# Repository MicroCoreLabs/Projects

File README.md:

# Ted Fried's MicroCore Labs Projects

My blog which has some details on these projects: www.MicroCoreLabs.Wordpress.com

My YouTube Channel with some videos of the stuff in action: www.youtube.com/channel/UC9B3TaEUon-araO2j7tp9jg/videos

Boards:

    MCL6809     -  Motorola 6809E emulator which runs on a Teensy 4.1 and can be used as a drop-in replacment 
    MCLZ8       -  Zilog Z80 emulator which runs on a Teensy 4.1 and can be used as a drop-in replacment 
    MCL86+      -  Intel 8088 emulator which runs on a Teensy 4.1 and can be used as a drop-in replacment 
    MCL86jr     -  IBMPCjr Accelerator which boosts performance to IBM PC/AT speed
    MCL65+      -  MOS 6502 emulator which runs on a Teensy 4.1 and can be used as a 6502 drop-in replacment
    MCL64       -  MOS 6510 emulator which runs on a Teensy 4.1 and can be used as a drop-in replacment in the Commodore 64
    MCL68+      -  Motorola 68000 emulator which runs on a Teensy 4.1 and can be used as a drop-in replacment 
    MCLV20_Max  -  NEC V20 drop-in replacment CPU which uses the MCL86+ board
	MCL8080+    -  Intel 8080 emulator which runs on an ATTiny85 and has a SPI interface as the local bus

Emulated Processors:

    MCL68  - Motorola 68000 Emulator written in C
    RISCV  - Simple and compact RISC-V RS32I implementation written in C
    MCL65  - MOS 6502 written in C

Microsequencer-based processors: 

    MCL65 - MOS 6502 
    MCL51 - Intel 8051
    MCL86 - Intel 8086/8088
    
Other processors:

    MCLR5 - Quad-Issue Superscalar RISCV
    Lockstep Quad Modular Redundant System 
    
Misc:

    Wheelwriter  - FPGA based Printer Option for the IBM Wheelwriter 5
    Wheelwriter2 - Arduino Leonardo based Printer Option for the IBM Wheelwriter 5
    Brother Typewriter - Arduino Leonardo converts Serial RX to a Brother Word Processor
    EPROM Emulator - Small PCB which uses Teensy 4.0 to emulate up a 64KB 27C512 EPROM
    MCL64_Tester - Extensive, menu-based, tests for the Commodore 64 motherboard
    MCLZ8 TRS-80 Emulator - Emulates a TRS-80 Model 1 inside of a Teensy microcontroller board
    MCL_TRS_NABU - Emulates a TRS-80 Model 1 using the MCLZ8 which runs inside of a NABU Personal Computer
    Turbo NABU - Uses the MCLZ8 to run simple C code on the Teensy to control the motherboard resources of the NABU Computer
    MDA Video - Project which uses an Arty Z7-20 SOC FPGA board to diaplay BMP images to an MDA display
    IBMPC_68000 - Uses the MCL86+ board to emulate a Motorola 68000 which runs inside of an IBM PC as-if they selected this processor in 1981
    MCL65_Apple1 - Converts an Apple II into an Appke 1 by emulating the BIOS PROMs, system memory, and performing some I/O conversion
	XTMax - 8-bit ISA card containing a Teensy 4.1 which can emulate RAM, ROM, and peripherals
        
For questions email me at www.MicroCoreLabs.com

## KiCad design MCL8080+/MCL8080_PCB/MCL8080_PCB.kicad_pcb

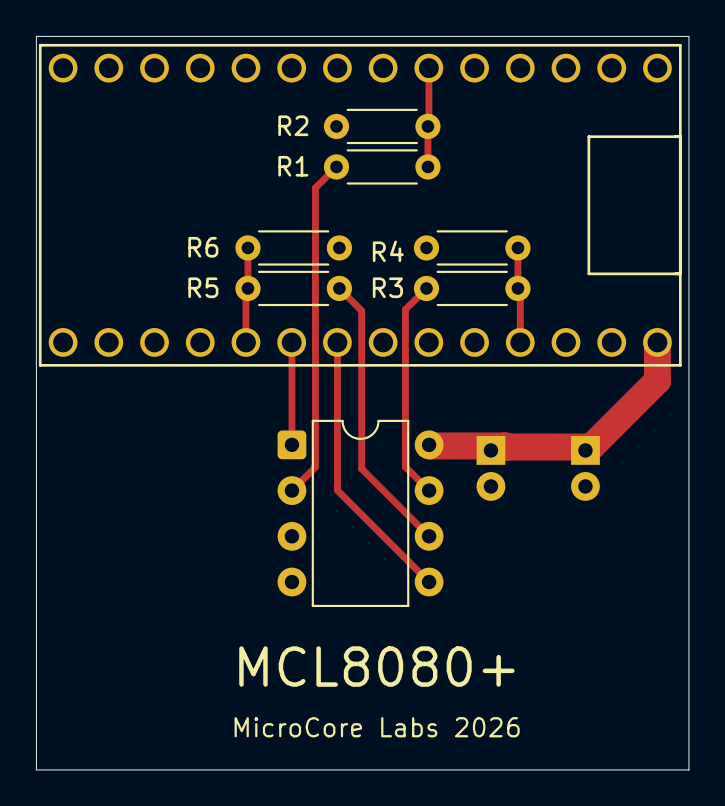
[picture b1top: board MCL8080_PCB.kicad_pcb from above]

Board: 2 copper layers, 36.2 x 40.8 mm, 10 parts (0 on the bottom side), 10 nets.

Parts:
C1: 0.1uF; CP_Radial_D5.0mm_P2.00mm
C2: 10 uF; CP_Radial_D5.0mm_P2.00mm
R1, R3, R5: 680; R_Axial_DIN0204_L3.6mm_D1.6mm_P5.08mm_Horizontal
R2, R4, R6: 1.2K; R_Axial_DIN0204_L3.6mm_D1.6mm_P5.08mm_Horizontal
U1: ATtiny85V-10P; DIP-8_W7.62mm
U2: Teensy4.0; Teensy40

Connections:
+5V: C1.1, C2.1, U1.8 (VCC), U2.33 (VIN)
GND: C1.2, C2.2, R2.1, R4.1, R6.1, U1.4 (GND), U2.1 (GND), U2.32 (GND)
RESET_n_3V: U1.1 (~RESET/PB5), U2.25 (18_A4_SDA0)
SPI_CLK_3V: R3.1, R4.2, U2.30 (23_A9_CRX1_MCLK1)
SPI_CLK_5V: R3.2, U1.7 (PB2)
SPI_CS_n_3V: R1.1, R2.2, U2.6 (4_BCLK2)
SPI_CS_n_5V: R1.2, U1.2 (XTAL1/PB3)
SPI_MISO_3V: U1.5 (AREF/PB0), U2.26 (19_A5_SCL0)
SPI_MOSI_3V: R5.1, R6.2, U2.24 (17_A3_TX4_SDA1)
SPI_MOSI_5V: R5.2, U1.6 (PB1)

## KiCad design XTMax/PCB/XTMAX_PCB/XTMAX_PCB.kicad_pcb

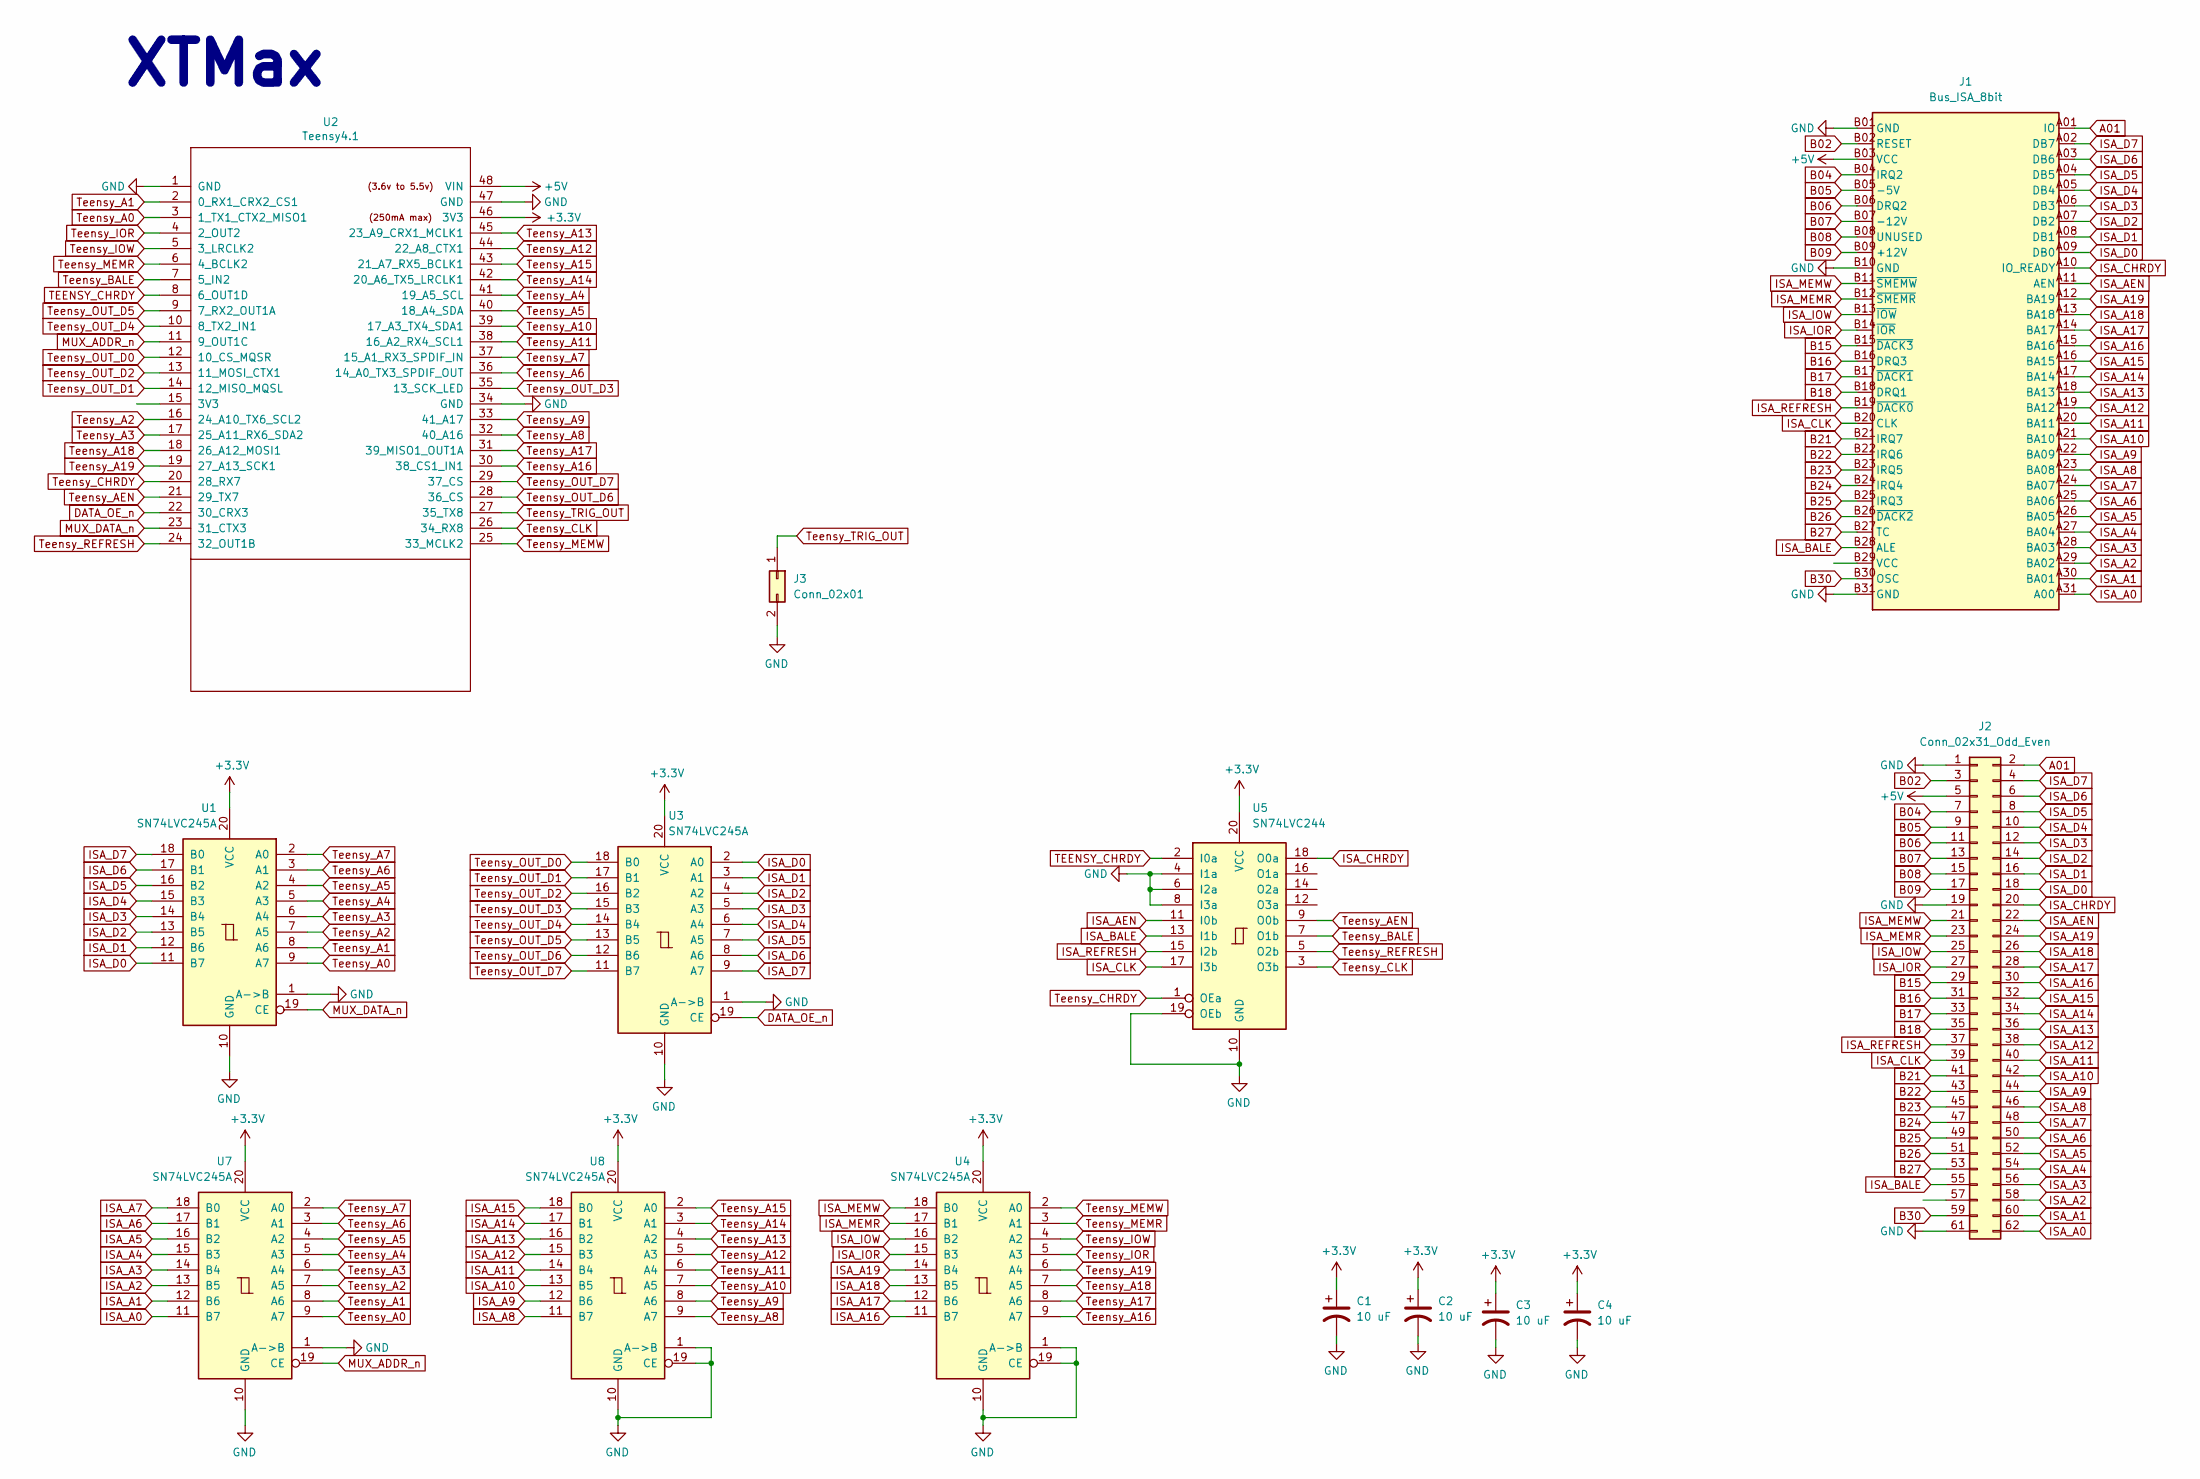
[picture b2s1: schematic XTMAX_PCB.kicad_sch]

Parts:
C1, C2, C3, C4: 10 uF; C_0402_1005Metric
J1: Bus_ISA_8bit; isa
J2: Conn_02x31_Odd_Even; PinHeader_2x31_P2.54mm_Vertical
J3: Conn_02x01; PinHeader_2x01_P2.54mm_Vertical
U1, U3, U4, U7, U8: SN74LVC245A; TSSOP-20_4.4x6.5mm_P0.65mm
U2: Teensy4.1; Teensy41_Ted_Modified
U5: SN74LVC244; TSSOP-20_4.4x6.5mm_P0.65mm

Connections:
+3V3: C1.1, C2.1, C3.1, C4.1, U1.20 (VCC), U2.46 (3V3), U3.20 (VCC), U4.20 (VCC), U5.20 (VCC), U7.20 (VCC), U8.20 (VCC)
+5V: J1.B03 (VCC), J2.5, U2.48 (VIN)
A01: J1.A01 (IO), J2.2
B02: J1.B02 (RESET), J2.3
B04: J1.B04 (IRQ2), J2.7
B05: J1.B05 (-5V), J2.9
B06: J1.B06 (DRQ2), J2.11
B07: J1.B07 (-12V), J2.13
B08: J1.B08 (UNUSED), J2.15
B09: J1.B09 (+12V), J2.17
B15: J1.B15 (~DACK3), J2.29
B16: J1.B16 (DRQ3), J2.31
B17: J1.B17 (~DACK1), J2.33
B18: J1.B18 (DRQ1), J2.35
B21: J1.B21 (IRQ7), J2.41
B22: J1.B22 (IRQ6), J2.43
B23: J1.B23 (IRQ5), J2.45
B24: J1.B24 (IRQ4), J2.47
B25: J1.B25 (IRQ3), J2.49
B26: J1.B26 (~DACK2), J2.51
B27: J1.B27 (TC), J2.53
B30: J1.B30 (OSC), J2.59
DATA_OE_n: U2.22 (30_CRX3), U3.19 (CE)
GND: C1.2, C2.2, C3.2, C4.2, J1.B01 (GND), J1.B10 (GND), J1.B31 (GND), J2.1, J2.19, J2.61, J3.2, U1.1 (A->B), U1.10 (GND), U2.1 (GND), U2.34 (GND), U2.47 (GND), U3.1 (A->B), U3.10 (GND), U4.1 (A->B), U4.10 (GND), U4.19 (CE), U5.4 (I1a), U5.6 (I2a), U5.8 (I3a), U5.10 (GND), U5.19 (OEb), U7.1 (A->B), U7.10 (GND), U8.1 (A->B), U8.10 (GND), U8.19 (CE)
ISA_A0: J1.A31 (A00), J2.62, U7.11 (B7)
ISA_A1: J1.A30 (BA01), J2.60, U7.12 (B6)
ISA_A2: J1.A29 (BA02), J2.58, U7.13 (B5)
ISA_A3: J1.A28 (BA03), J2.56, U7.14 (B4)
ISA_A4: J1.A27 (BA04), J2.54, U7.15 (B3)
ISA_A5: J1.A26 (BA05), J2.52, U7.16 (B2)
ISA_A6: J1.A25 (BA06), J2.50, U7.17 (B1)
ISA_A7: J1.A24 (BA07), J2.48, U7.18 (B0)
ISA_A8: J1.A23 (BA08), J2.46, U8.11 (B7)
ISA_A9: J1.A22 (BA09), J2.44, U8.12 (B6)
ISA_A10: J1.A21 (BA10), J2.42, U8.13 (B5)
ISA_A11: J1.A20 (BA11), J2.40, U8.14 (B4)
ISA_A12: J1.A19 (BA12), J2.38, U8.15 (B3)
ISA_A13: J1.A18 (BA13), J2.36, U8.16 (B2)
ISA_A14: J1.A17 (BA14), J2.34, U8.17 (B1)
ISA_A15: J1.A16 (BA15), J2.32, U8.18 (B0)
ISA_A16: J1.A15 (BA16), J2.30, U4.11 (B7)
ISA_A17: J1.A14 (BA17), J2.28, U4.12 (B6)
ISA_A18: J1.A13 (BA18), J2.26, U4.13 (B5)
ISA_A19: J1.A12 (BA19), J2.24, U4.14 (B4)
ISA_AEN: J1.A11 (AEN), J2.22, U5.11 (I0b)
ISA_BALE: J1.B28 (ALE), J2.55, U5.13 (I1b)
ISA_CHRDY: J1.A10 (IO_READY), J2.20, U5.18 (O0a)
ISA_CLK: J1.B20 (CLK), J2.39, U5.17 (I3b)
ISA_D0: J1.A09 (DB0), J2.18, U1.11 (B7), U3.2 (A0)
ISA_D1: J1.A08 (DB1), J2.16, U1.12 (B6), U3.3 (A1)
ISA_D2: J1.A07 (DB2), J2.14, U1.13 (B5), U3.4 (A2)
ISA_D3: J1.A06 (DB3), J2.12, U1.14 (B4), U3.5 (A3)
ISA_D4: J1.A05 (DB4), J2.10, U1.15 (B3), U3.6 (A4)
ISA_D5: J1.A04 (DB5), J2.8, U1.16 (B2), U3.7 (A5)
ISA_D6: J1.A03 (DB6), J2.6, U1.17 (B1), U3.8 (A6)
ISA_D7: J1.A02 (DB7), J2.4, U1.18 (B0), U3.9 (A7)
ISA_IOR: J1.B14 (~IOR), J2.27, U4.15 (B3)
ISA_IOW: J1.B13 (~IOW), J2.25, U4.16 (B2)
ISA_MEMR: J1.B12 (~SMEMR), J2.23, U4.17 (B1)
ISA_MEMW: J1.B11 (~SMEMW), J2.21, U4.18 (B0)
ISA_REFRESH: J1.B19 (~DACK0), J2.37, U5.15 (I2b)
MUX_ADDR_n: U2.11 (9_OUT1C), U7.19 (CE)
MUX_DATA_n: U1.19 (CE), U2.23 (31_CTX3)
TEENSY_CHRDY: U2.8 (6_OUT1D), U5.2 (I0a)
Teensy_A0: U1.9 (A7), U2.3 (1_TX1_CTX2_MISO1), U7.9 (A7)
Teensy_A1: U1.8 (A6), U2.2 (0_RX1_CRX2_CS1), U7.8 (A6)
Teensy_A2: U1.7 (A5), U2.16 (24_A10_TX6_SCL2), U7.7 (A5)
Teensy_A3: U1.6 (A4), U2.17 (25_A11_RX6_SDA2), U7.6 (A4)
Teensy_A4: U1.5 (A3), U2.41 (19_A5_SCL), U7.5 (A3)
Teensy_A5: U1.4 (A2), U2.40 (18_A4_SDA), U7.4 (A2)
Teensy_A6: U1.3 (A1), U2.36 (14_A0_TX3_SPDIF_OUT), U7.3 (A1)
Teensy_A7: U1.2 (A0), U2.37 (15_A1_RX3_SPDIF_IN), U7.2 (A0)
Teensy_A8: U2.32 (40_A16), U8.9 (A7)
Teensy_A9: U2.33 (41_A17), U8.8 (A6)
Teensy_A10: U2.39 (17_A3_TX4_SDA1), U8.7 (A5)
Teensy_A11: U2.38 (16_A2_RX4_SCL1), U8.6 (A4)
Teensy_A12: U2.44 (22_A8_CTX1), U8.5 (A3)
Teensy_A13: U2.45 (23_A9_CRX1_MCLK1), U8.4 (A2)
Teensy_A14: U2.42 (20_A6_TX5_LRCLK1), U8.3 (A1)
Teensy_A15: U2.43 (21_A7_RX5_BCLK1), U8.2 (A0)
Teensy_A16: U2.30 (38_CS1_IN1), U4.9 (A7)
Teensy_A17: U2.31 (39_MISO1_OUT1A), U4.8 (A6)
Teensy_A18: U2.18 (26_A12_MOSI1), U4.7 (A5)
Teensy_A19: U2.19 (27_A13_SCK1), U4.6 (A4)
Teensy_AEN: U2.21 (29_TX7), U5.9 (O0b)
Teensy_BALE: U2.7 (5_IN2), U5.7 (O1b)
Teensy_CHRDY: U2.20 (28_RX7), U5.1 (OEa)
Teensy_CLK: U2.26 (34_RX8), U5.3 (O3b)
Teensy_IOR: U2.4 (2_OUT2), U4.5 (A3)
Teensy_IOW: U2.5 (3_LRCLK2), U4.4 (A2)
Teensy_MEMR: U2.6 (4_BCLK2), U4.3 (A1)
Teensy_MEMW: U2.25 (33_MCLK2), U4.2 (A0)
Teensy_OUT_D0: U2.12 (10_CS_MQSR), U3.18 (B0)
Teensy_OUT_D1: U2.14 (12_MISO_MQSL), U3.17 (B1)
Teensy_OUT_D2: U2.13 (11_MOSI_CTX1), U3.16 (B2)
Teensy_OUT_D3: U2.35 (13_SCK_LED), U3.15 (B3)
Teensy_OUT_D4: U2.10 (8_TX2_IN1), U3.14 (B4)
Teensy_OUT_D5: U2.9 (7_RX2_OUT1A), U3.13 (B5)
Teensy_OUT_D6: U2.28 (36_CS), U3.12 (B6)
Teensy_OUT_D7: U2.29 (37_CS), U3.11 (B7)
Teensy_REFRESH: U2.24 (32_OUT1B), U5.5 (O2b)
Teensy_TRIG_OUT: J3.1, U2.27 (35_TX8)

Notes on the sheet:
XTMax

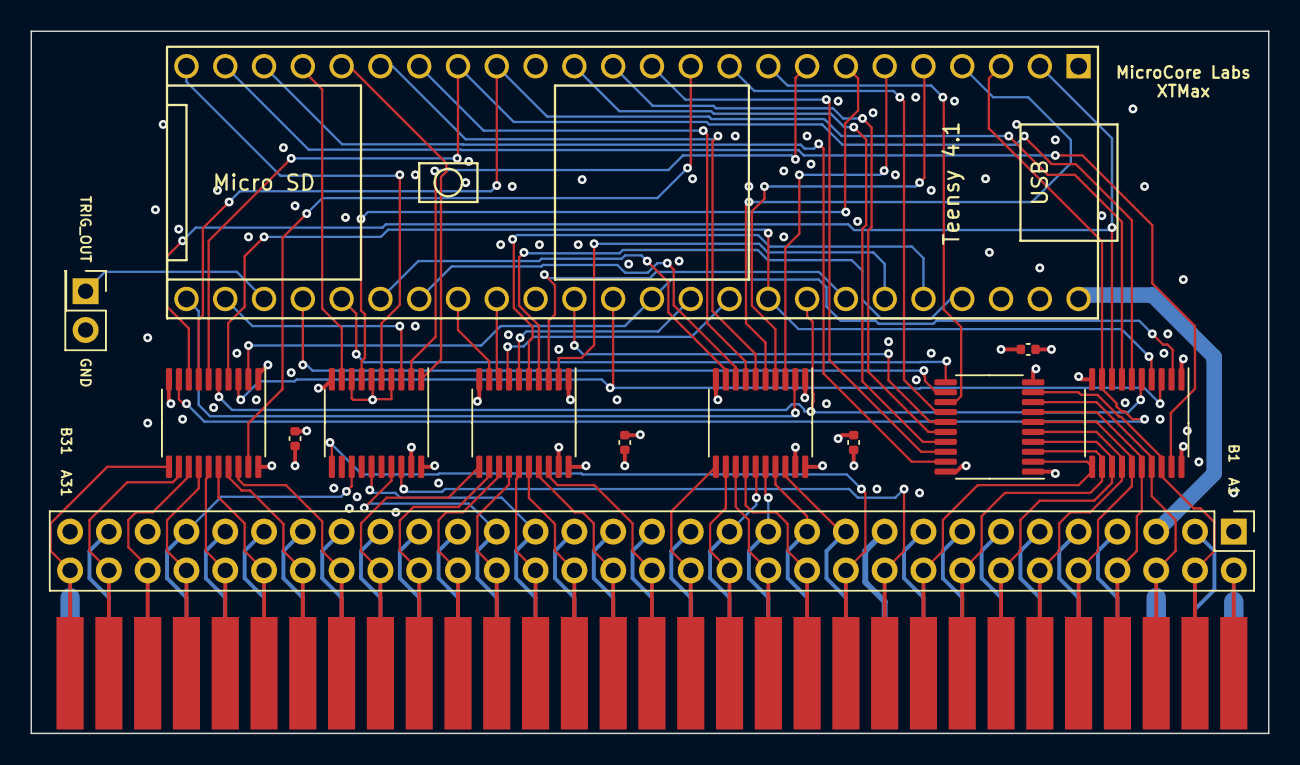
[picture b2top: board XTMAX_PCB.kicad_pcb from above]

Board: 4 copper layers, 81.0 x 46.0 mm, 14 parts (0 on the bottom side), 102 nets.

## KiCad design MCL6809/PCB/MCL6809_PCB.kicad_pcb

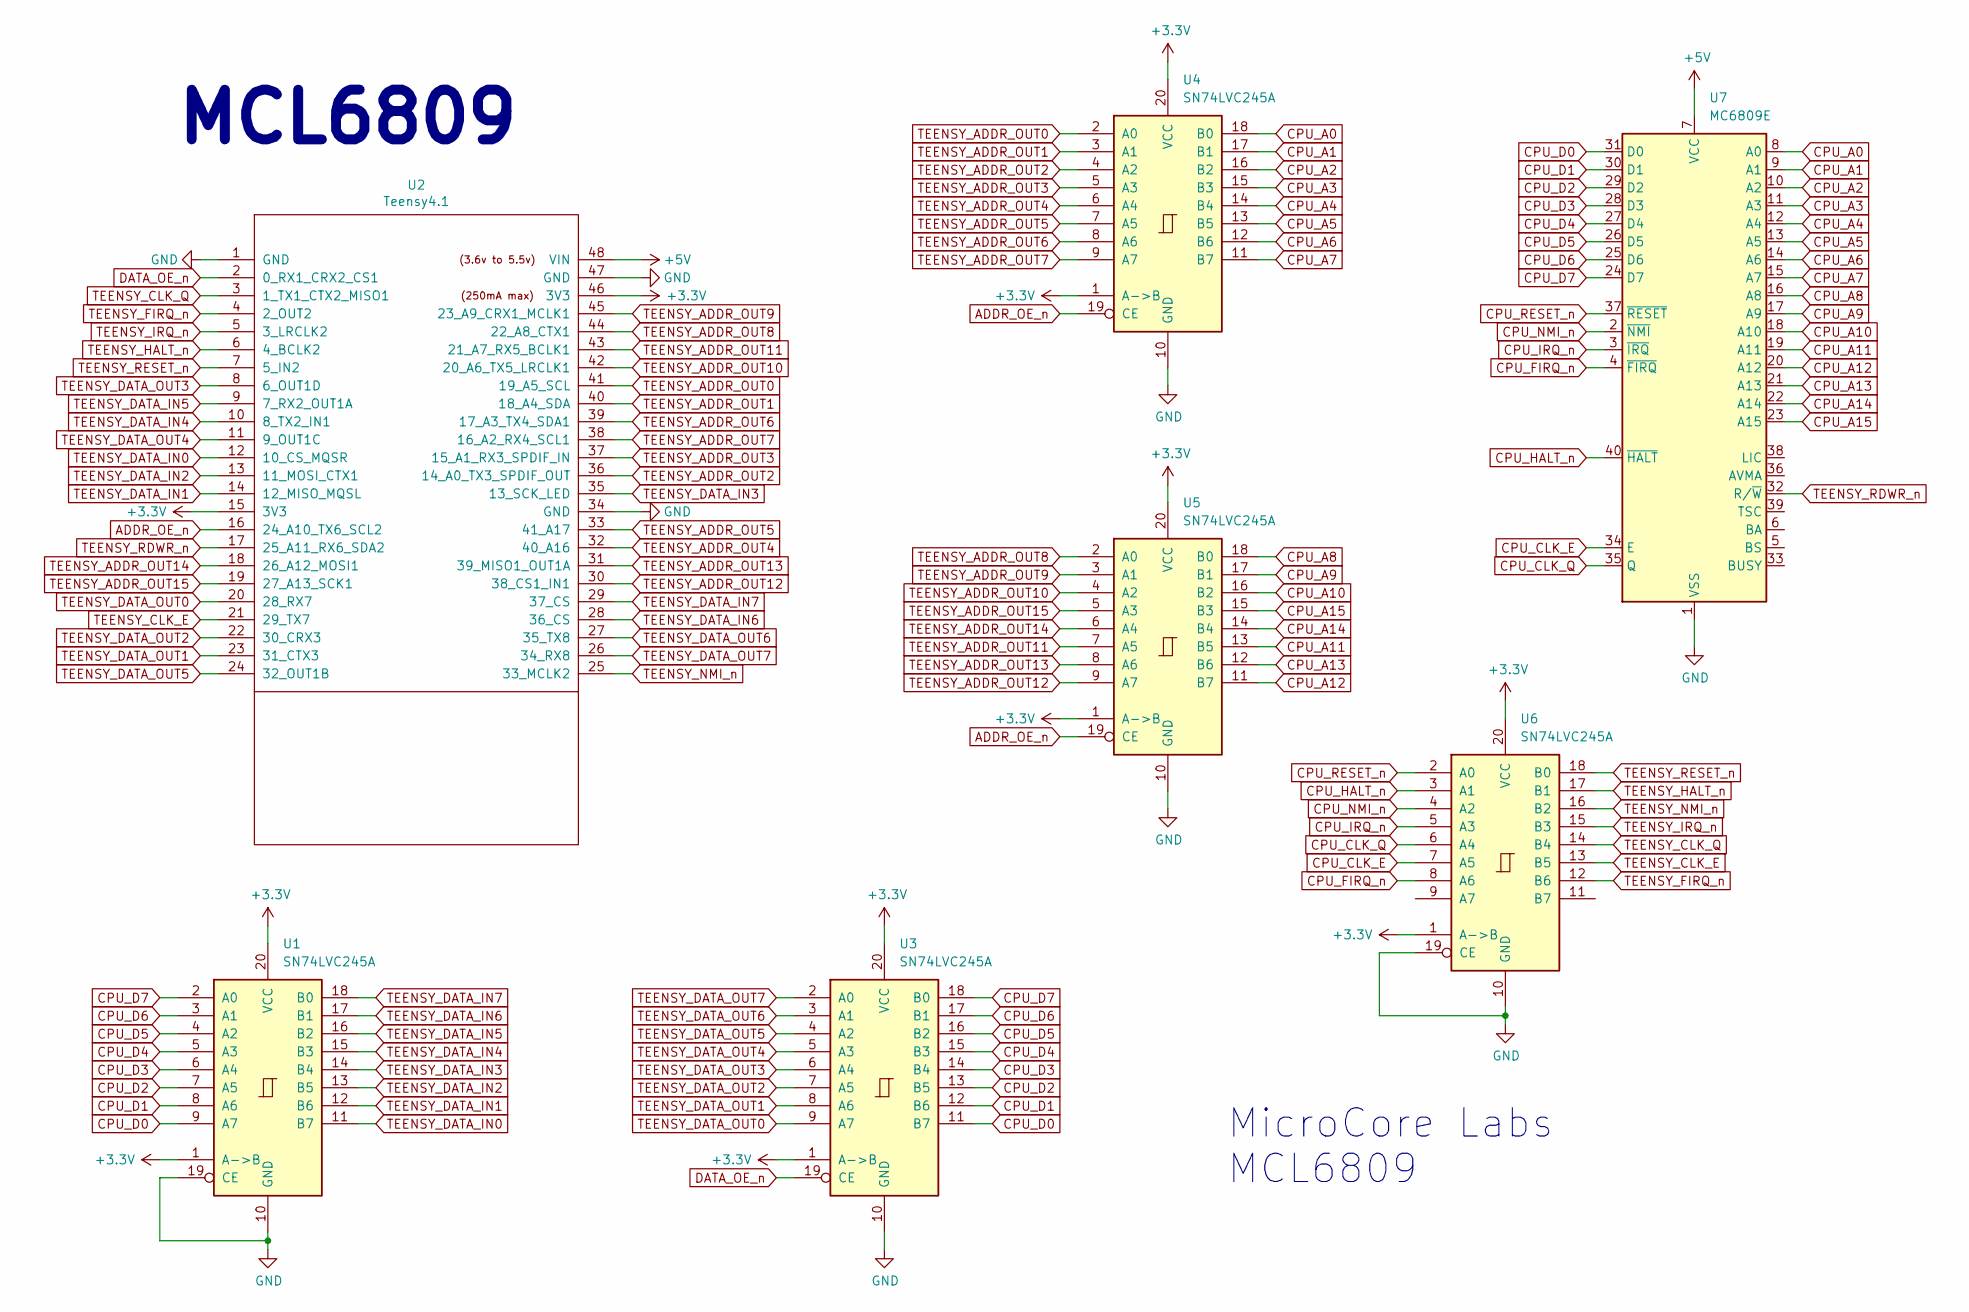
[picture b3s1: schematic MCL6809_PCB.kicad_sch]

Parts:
U1, U3, U4, U5, U6: SN74LVC245A; TSSOP-20_4.4x6.5mm_P0.65mm
U2: Teensy4.1; Teensy41_Ted_Modified
U7: MC6809E; DIP-40_W15.24mm

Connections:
+3V3: U1.1 (A->B), U1.20 (VCC), U2.15 (3V3), U2.46 (3V3), U3.1 (A->B), U3.20 (VCC), U4.1 (A->B), U4.20 (VCC), U5.1 (A->B), U5.20 (VCC), U6.1 (A->B), U6.20 (VCC)
+5V: U2.48 (VIN), U7.7 (VCC)
ADDR_OE_n: U2.16 (24_A10_TX6_SCL2), U4.19 (CE), U5.19 (CE)
CPU_A0: U4.18 (B0), U7.8 (A0)
CPU_A1: U4.17 (B1), U7.9 (A1)
CPU_A2: U4.16 (B2), U7.10 (A2)
CPU_A3: U4.15 (B3), U7.11 (A3)
CPU_A4: U4.14 (B4), U7.12 (A4)
CPU_A5: U4.13 (B5), U7.13 (A5)
CPU_A6: U4.12 (B6), U7.14 (A6)
CPU_A7: U4.11 (B7), U7.15 (A7)
CPU_A8: U5.18 (B0), U7.16 (A8)
CPU_A9: U5.17 (B1), U7.17 (A9)
CPU_A10: U5.16 (B2), U7.18 (A10)
CPU_A11: U5.13 (B5), U7.19 (A11)
CPU_A12: U5.11 (B7), U7.20 (A12)
CPU_A13: U5.12 (B6), U7.21 (A13)
CPU_A14: U5.14 (B4), U7.22 (A14)
CPU_A15: U5.15 (B3), U7.23 (A15)
CPU_CLK_E: U6.7 (A5), U7.34 (E)
CPU_CLK_Q: U6.6 (A4), U7.35 (Q)
CPU_D0: U1.9 (A7), U3.11 (B7), U7.31 (D0)
CPU_D1: U1.8 (A6), U3.12 (B6), U7.30 (D1)
CPU_D2: U1.7 (A5), U3.13 (B5), U7.29 (D2)
CPU_D3: U1.6 (A4), U3.14 (B4), U7.28 (D3)
CPU_D4: U1.5 (A3), U3.15 (B3), U7.27 (D4)
CPU_D5: U1.4 (A2), U3.16 (B2), U7.26 (D5)
CPU_D6: U1.3 (A1), U3.17 (B1), U7.25 (D6)
CPU_D7: U1.2 (A0), U3.18 (B0), U7.24 (D7)
CPU_FIRQ_n: U6.8 (A6), U7.4 (~FIRQ)
CPU_HALT_n: U6.3 (A1), U7.40 (~HALT)
CPU_IRQ_n: U6.5 (A3), U7.3 (~IRQ)
CPU_NMI_n: U6.4 (A2), U7.2 (~NMI)
CPU_RESET_n: U6.2 (A0), U7.37 (~RESET)
DATA_OE_n: U2.2 (0_RX1_CRX2_CS1), U3.19 (CE)
GND: U1.10 (GND), U1.19 (CE), U2.1 (GND), U2.34 (GND), U2.47 (GND), U3.10 (GND), U4.10 (GND), U5.10 (GND), U6.10 (GND), U6.19 (CE), U7.1 (VSS)
TEENSY_ADDR_OUT0: U2.41 (19_A5_SCL), U4.2 (A0)
TEENSY_ADDR_OUT1: U2.40 (18_A4_SDA), U4.3 (A1)
TEENSY_ADDR_OUT2: U2.36 (14_A0_TX3_SPDIF_OUT), U4.4 (A2)
TEENSY_ADDR_OUT3: U2.37 (15_A1_RX3_SPDIF_IN), U4.5 (A3)
TEENSY_ADDR_OUT4: U2.32 (40_A16), U4.6 (A4)
TEENSY_ADDR_OUT5: U2.33 (41_A17), U4.7 (A5)
TEENSY_ADDR_OUT6: U2.39 (17_A3_TX4_SDA1), U4.8 (A6)
TEENSY_ADDR_OUT7: U2.38 (16_A2_RX4_SCL1), U4.9 (A7)
TEENSY_ADDR_OUT8: U2.44 (22_A8_CTX1), U5.2 (A0)
TEENSY_ADDR_OUT9: U2.45 (23_A9_CRX1_MCLK1), U5.3 (A1)
TEENSY_ADDR_OUT10: U2.42 (20_A6_TX5_LRCLK1), U5.4 (A2)
TEENSY_ADDR_OUT11: U2.43 (21_A7_RX5_BCLK1), U5.7 (A5)
TEENSY_ADDR_OUT12: U2.30 (38_CS1_IN1), U5.9 (A7)
TEENSY_ADDR_OUT13: U2.31 (39_MISO1_OUT1A), U5.8 (A6)
TEENSY_ADDR_OUT14: U2.18 (26_A12_MOSI1), U5.6 (A4)
TEENSY_ADDR_OUT15: U2.19 (27_A13_SCK1), U5.5 (A3)
TEENSY_CLK_E: U2.21 (29_TX7), U6.13 (B5)
TEENSY_CLK_Q: U2.3 (1_TX1_CTX2_MISO1), U6.14 (B4)
TEENSY_DATA_IN0: U1.11 (B7), U2.12 (10_CS_MQSR)
TEENSY_DATA_IN1: U1.12 (B6), U2.14 (12_MISO_MQSL)
TEENSY_DATA_IN2: U1.13 (B5), U2.13 (11_MOSI_CTX1)
TEENSY_DATA_IN3: U1.14 (B4), U2.35 (13_SCK_LED)
TEENSY_DATA_IN4: U1.15 (B3), U2.10 (8_TX2_IN1)
TEENSY_DATA_IN5: U1.16 (B2), U2.9 (7_RX2_OUT1A)
TEENSY_DATA_IN6: U1.17 (B1), U2.28 (36_CS)
TEENSY_DATA_IN7: U1.18 (B0), U2.29 (37_CS)
TEENSY_DATA_OUT0: U2.20 (28_RX7), U3.9 (A7)
TEENSY_DATA_OUT1: U2.23 (31_CTX3), U3.8 (A6)
TEENSY_DATA_OUT2: U2.22 (30_CRX3), U3.7 (A5)
TEENSY_DATA_OUT3: U2.8 (6_OUT1D), U3.6 (A4)
TEENSY_DATA_OUT4: U2.11 (9_OUT1C), U3.5 (A3)
TEENSY_DATA_OUT5: U2.24 (32_OUT1B), U3.4 (A2)
TEENSY_DATA_OUT6: U2.27 (35_TX8), U3.3 (A1)
TEENSY_DATA_OUT7: U2.26 (34_RX8), U3.2 (A0)
TEENSY_FIRQ_n: U2.4 (2_OUT2), U6.12 (B6)
TEENSY_HALT_n: U2.6 (4_BCLK2), U6.17 (B1)
TEENSY_IRQ_n: U2.5 (3_LRCLK2), U6.15 (B3)
TEENSY_NMI_n: U2.25 (33_MCLK2), U6.16 (B2)
TEENSY_RDWR_n: U2.17 (25_A11_RX6_SDA2), U7.32 (R/~W)
TEENSY_RESET_n: U2.7 (5_IN2), U6.18 (B0)

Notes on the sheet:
MicroCore Labs MCL6809
MCL6809

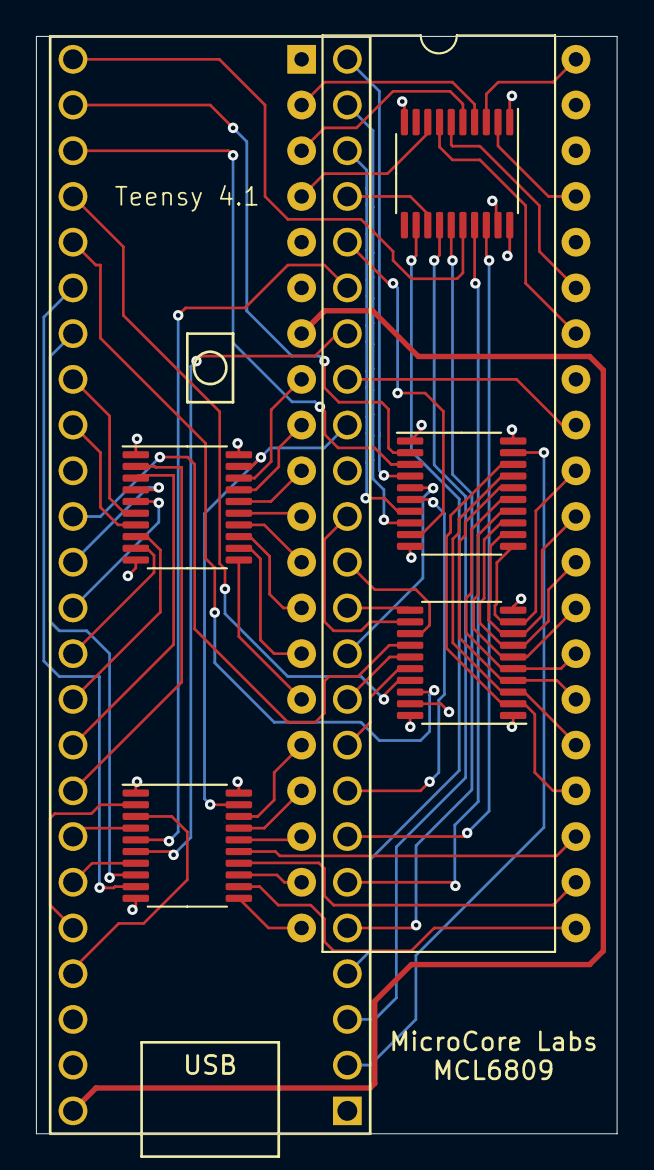
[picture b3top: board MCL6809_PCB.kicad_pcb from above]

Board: 4 copper layers, 32.3 x 61.0 mm, 7 parts (0 on the bottom side), 76 nets.

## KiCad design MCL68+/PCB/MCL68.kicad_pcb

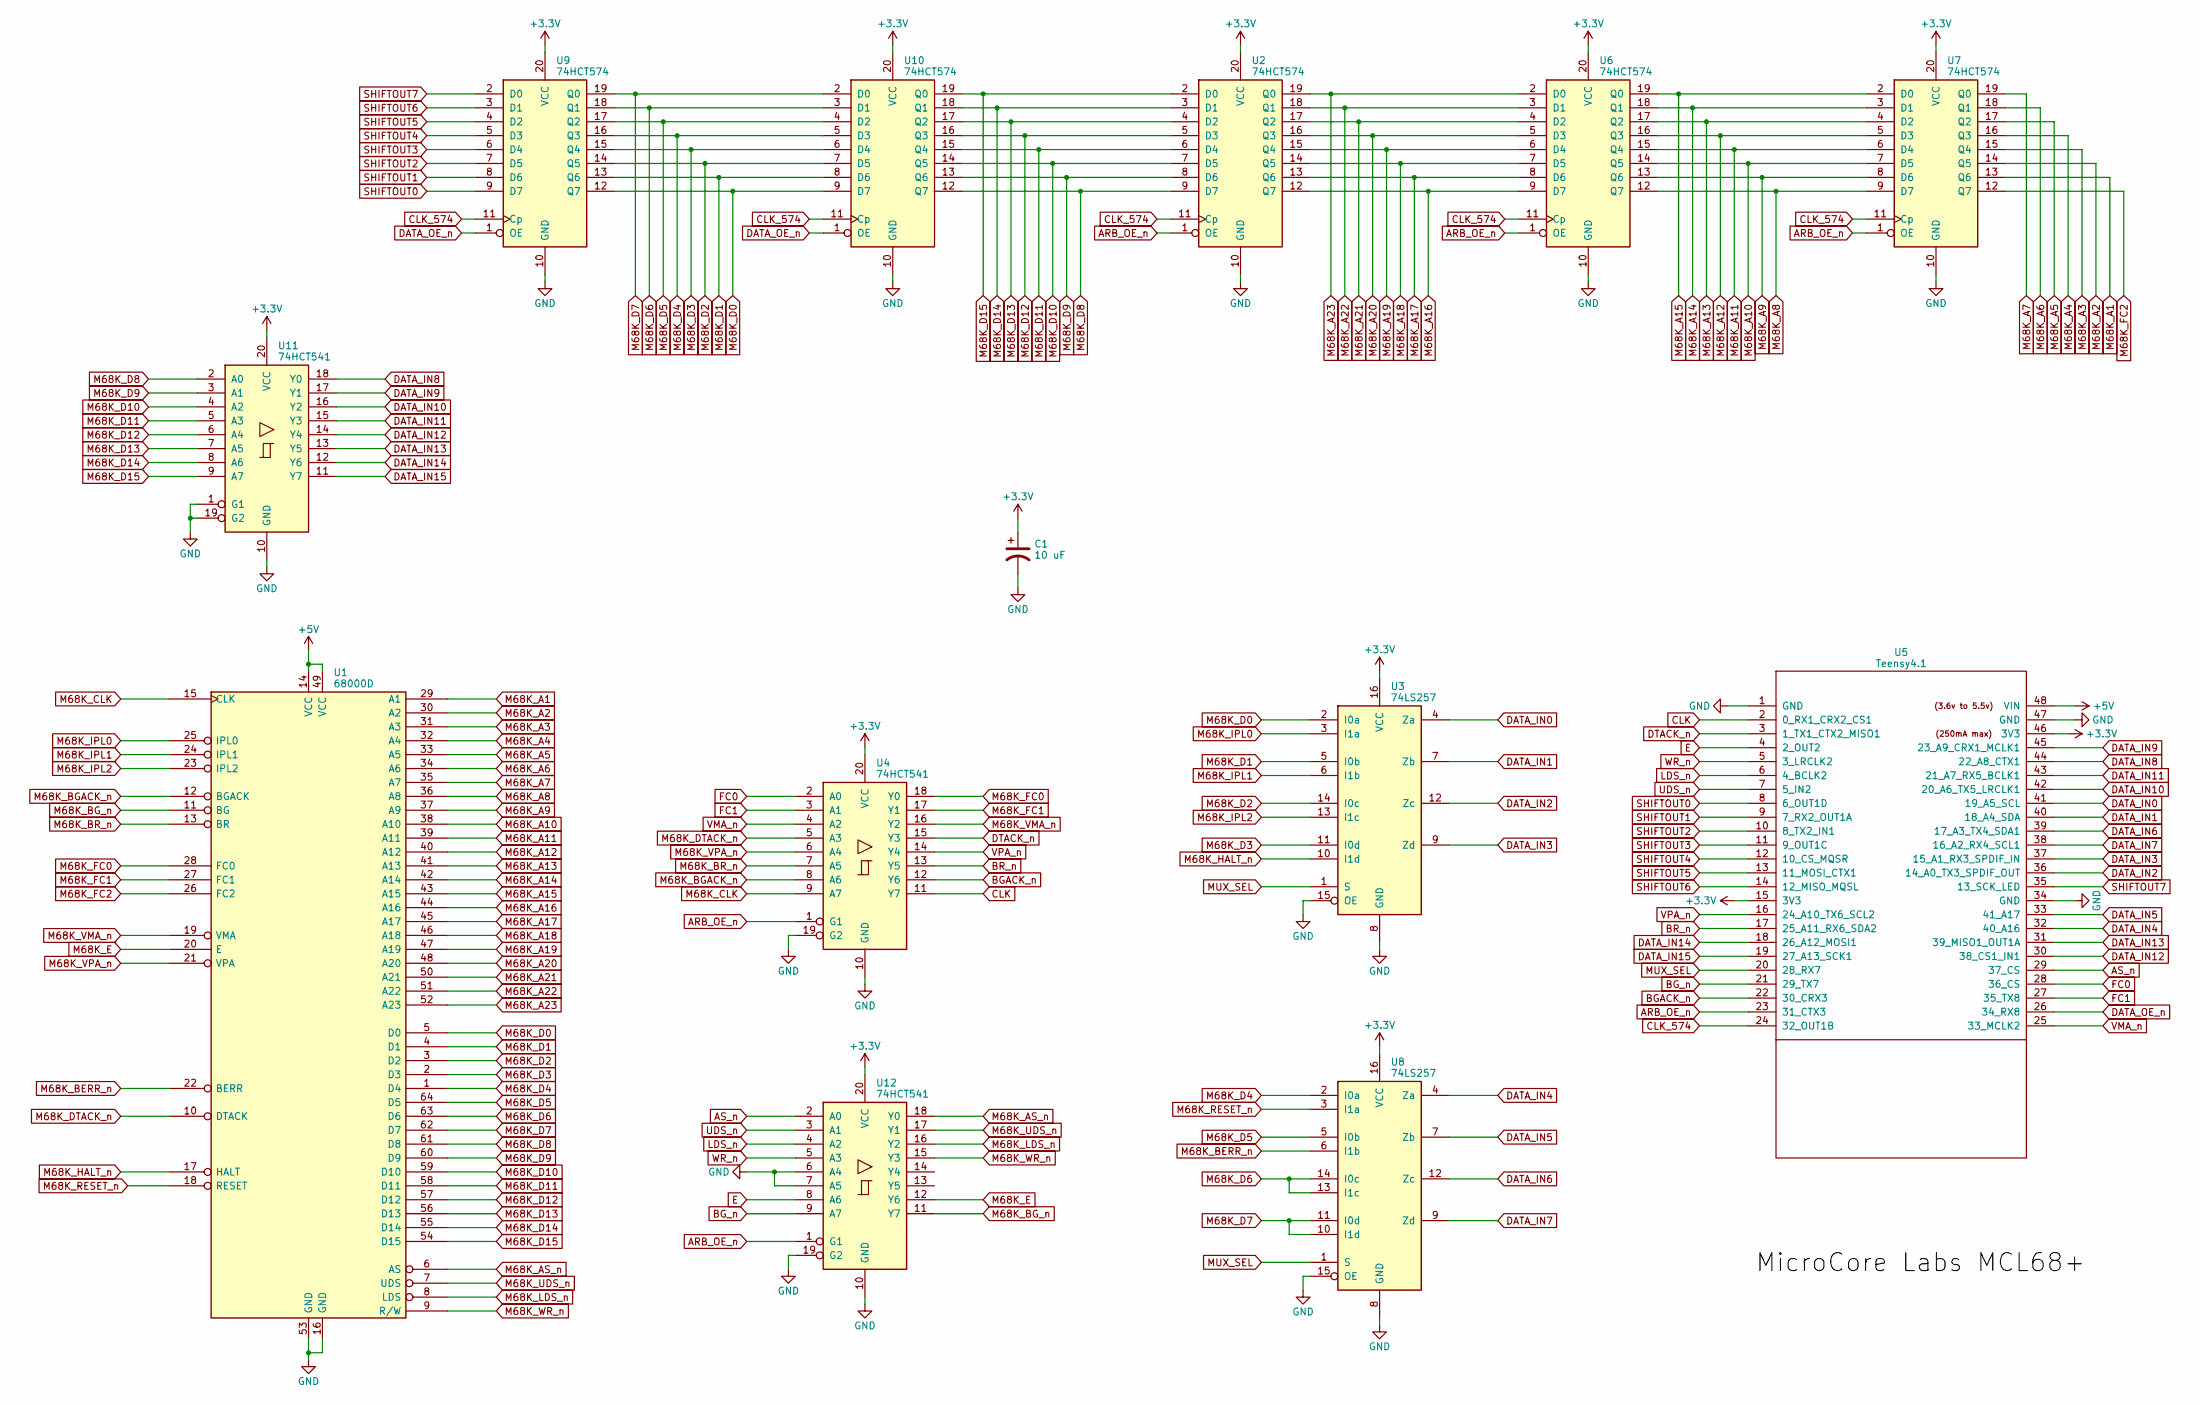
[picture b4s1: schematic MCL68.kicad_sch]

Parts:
C1: 10 uF; C_0805_2012Metric
U1: 68000D; DIP-64_W25.4mm
U2, U6, U7, U9, U10: 74HCT574; TSSOP-20_4.4x6.5mm_P0.65mm
U3, U8: 74LS257; TSSOP-16_4.4x5mm_P0.65mm
U4, U11, U12: 74HCT541; TSSOP-20_4.4x6.5mm_P0.65mm
U5: Teensy4.1; DIP-48_W15.24mm

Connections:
+3.3V: C1.1, U2.20 (VCC), U3.16 (VCC), U4.20 (VCC), U5.15 (3V3), U5.46 (3V3), U6.20 (VCC), U7.20 (VCC), U8.16 (VCC), U9.20 (VCC), U10.20 (VCC), U11.20 (VCC), U12.20 (VCC)
+5V: U1.14 (VCC), U1.49 (VCC), U5.48 (VIN)
ARB_OE_n: U2.1 (OE), U4.1 (G1), U5.23 (31_CTX3), U6.1 (OE), U7.1 (OE), U12.1 (G1)
AS_n: U5.29 (37_CS), U12.2 (A0)
BGACK_n: U4.12 (Y6), U5.22 (30_CRX3)
BG_n: U5.21 (29_TX7), U12.9 (A7)
BR_n: U4.13 (Y5), U5.17 (25_A11_RX6_SDA2)
CLK: U4.11 (Y7), U5.2 (0_RX1_CRX2_CS1)
CLK_574: U2.11 (Cp), U5.24 (32_OUT1B), U6.11 (Cp), U7.11 (Cp), U9.11 (Cp), U10.11 (Cp)
DATA_IN0: U3.4 (Za), U5.41 (19_A5_SCL)
DATA_IN1: U3.7 (Zb), U5.40 (18_A4_SDA)
DATA_IN2: U3.12 (Zc), U5.36 (14_A0_TX3_SPDIF_OUT)
DATA_IN3: U3.9 (Zd), U5.37 (15_A1_RX3_SPDIF_IN)
DATA_IN4: U5.32 (40_A16), U8.4 (Za)
DATA_IN5: U5.33 (41_A17), U8.7 (Zb)
DATA_IN6: U5.39 (17_A3_TX4_SDA1), U8.12 (Zc)
DATA_IN7: U5.38 (16_A2_RX4_SCL1), U8.9 (Zd)
DATA_IN8: U5.44 (22_A8_CTX1), U11.18 (Y0)
DATA_IN9: U5.45 (23_A9_CRX1_MCLK1), U11.17 (Y1)
DATA_IN10: U5.42 (20_A6_TX5_LRCLK1), U11.16 (Y2)
DATA_IN11: U5.43 (21_A7_RX5_BCLK1), U11.15 (Y3)
DATA_IN12: U5.30 (38_CS1_IN1), U11.14 (Y4)
DATA_IN13: U5.31 (39_MISO1_OUT1A), U11.13 (Y5)
DATA_IN14: U5.18 (26_A12_MOSI1), U11.12 (Y6)
DATA_IN15: U5.19 (27_A13_SCK1), U11.11 (Y7)
DATA_OE_n: U5.26 (34_RX8), U9.1 (OE), U10.1 (OE)
DTACK_n: U4.15 (Y3), U5.3 (1_TX1_CTX2_MISO1)
E: U5.4 (2_OUT2), U12.8 (A6)
FC0: U4.2 (A0), U5.28 (36_CS)
FC1: U4.3 (A1), U5.27 (35_TX8)
GND: C1.2, U1.16 (GND), U1.53 (GND), U2.10 (GND), U3.8 (GND), U3.15 (OE), U4.10 (GND), U4.19 (G2), U5.1 (GND), U5.34 (GND), U5.47 (GND), U6.10 (GND), U7.10 (GND), U8.8 (GND), U8.15 (OE), U9.10 (GND), U10.10 (GND), U11.1 (G1), U11.10 (GND), U11.19 (G2), U12.6 (A4), U12.7 (A5), U12.10 (GND), U12.19 (G2)
LDS_n: U5.6 (4_BCLK2), U12.4 (A2)
M68K_A1: U1.29 (A1), U7.13 (Q6)
M68K_A2: U1.30 (A2), U7.14 (Q5)
M68K_A3: U1.31 (A3), U7.15 (Q4)
M68K_A4: U1.32 (A4), U7.16 (Q3)
M68K_A5: U1.33 (A5), U7.17 (Q2)
M68K_A6: U1.34 (A6), U7.18 (Q1)
M68K_A7: U1.35 (A7), U7.19 (Q0)
M68K_A8: U1.36 (A8), U6.12 (Q7), U7.9 (D7)
M68K_A9: U1.37 (A9), U6.13 (Q6), U7.8 (D6)
M68K_A10: U1.38 (A10), U6.14 (Q5), U7.7 (D5)
M68K_A11: U1.39 (A11), U6.15 (Q4), U7.6 (D4)
M68K_A12: U1.40 (A12), U6.16 (Q3), U7.5 (D3)
M68K_A13: U1.41 (A13), U6.17 (Q2), U7.4 (D2)
M68K_A14: U1.42 (A14), U6.18 (Q1), U7.3 (D1)
M68K_A15: U1.43 (A15), U6.19 (Q0), U7.2 (D0)
M68K_A16: U1.44 (A16), U2.12 (Q7), U6.9 (D7)
M68K_A17: U1.45 (A17), U2.13 (Q6), U6.8 (D6)
M68K_A18: U1.46 (A18), U2.14 (Q5), U6.7 (D5)
M68K_A19: U1.47 (A19), U2.15 (Q4), U6.6 (D4)
M68K_A20: U1.48 (A20), U2.16 (Q3), U6.5 (D3)
M68K_A21: U1.50 (A21), U2.17 (Q2), U6.4 (D2)
M68K_A22: U1.51 (A22), U2.18 (Q1), U6.3 (D1)
M68K_A23: U1.52 (A23), U2.19 (Q0), U6.2 (D0)
M68K_AS_n: U1.6 (AS), U12.18 (Y0)
M68K_BERR_n: U1.22 (BERR), U8.6 (I1b)
M68K_BGACK_n: U1.12 (BGACK), U4.8 (A6)
M68K_BG_n: U1.11 (BG), U12.11 (Y7)
M68K_BR_n: U1.13 (BR), U4.7 (A5)
M68K_CLK: U1.15 (CLK), U4.9 (A7)
M68K_D0: U1.5 (D0), U3.2 (I0a), U9.12 (Q7), U10.9 (D7)
M68K_D1: U1.4 (D1), U3.5 (I0b), U9.13 (Q6), U10.8 (D6)
M68K_D2: U1.3 (D2), U3.14 (I0c), U9.14 (Q5), U10.7 (D5)
M68K_D3: U1.2 (D3), U3.11 (I0d), U9.15 (Q4), U10.6 (D4)
M68K_D4: U1.1 (D4), U8.2 (I0a), U9.16 (Q3), U10.5 (D3)
M68K_D5: U1.64 (D5), U8.5 (I0b), U9.17 (Q2), U10.4 (D2)
M68K_D6: U1.63 (D6), U8.13 (I1c), U8.14 (I0c), U9.18 (Q1), U10.3 (D1)
M68K_D7: U1.62 (D7), U8.10 (I1d), U8.11 (I0d), U9.19 (Q0), U10.2 (D0)
M68K_D8: U1.61 (D8), U2.9 (D7), U10.12 (Q7), U11.2 (A0)
M68K_D9: U1.60 (D9), U2.8 (D6), U10.13 (Q6), U11.3 (A1)
M68K_D10: U1.59 (D10), U2.7 (D5), U10.14 (Q5), U11.4 (A2)
M68K_D11: U1.58 (D11), U2.6 (D4), U10.15 (Q4), U11.5 (A3)
M68K_D12: U1.57 (D12), U2.5 (D3), U10.16 (Q3), U11.6 (A4)
M68K_D13: U1.56 (D13), U2.4 (D2), U10.17 (Q2), U11.7 (A5)
M68K_D14: U1.55 (D14), U2.3 (D1), U10.18 (Q1), U11.8 (A6)
M68K_D15: U1.54 (D15), U2.2 (D0), U10.19 (Q0), U11.9 (A7)
M68K_DTACK_n: U1.10 (DTACK), U4.5 (A3)
M68K_E: U1.20 (E), U12.12 (Y6)
M68K_FC0: U1.28 (FC0), U4.18 (Y0)
M68K_FC1: U1.27 (FC1), U4.17 (Y1)
M68K_FC2: U1.26 (FC2), U7.12 (Q7)
M68K_HALT_n: U1.17 (HALT), U3.10 (I1d)
M68K_IPL0: U1.25 (IPL0), U3.3 (I1a)
M68K_IPL1: U1.24 (IPL1), U3.6 (I1b)
M68K_IPL2: U1.23 (IPL2), U3.13 (I1c)
M68K_LDS_n: U1.8 (LDS), U12.16 (Y2)
M68K_RESET_n: U1.18 (RESET), U8.3 (I1a)
M68K_UDS_n: U1.7 (UDS), U12.17 (Y1)
M68K_VMA_n: U1.19 (VMA), U4.16 (Y2)
M68K_VPA_n: U1.21 (VPA), U4.6 (A4)
M68K_WR_n: U1.9 (R/W), U12.15 (Y3)
MUX_SEL: U3.1 (S), U5.20 (28_RX7), U8.1 (S)
SHIFTOUT0: U5.8 (6_OUT1D), U9.9 (D7)
SHIFTOUT1: U5.9 (7_RX2_OUT1A), U9.8 (D6)
SHIFTOUT2: U5.10 (8_TX2_IN1), U9.7 (D5)
SHIFTOUT3: U5.11 (9_OUT1C), U9.6 (D4)
SHIFTOUT4: U5.12 (10_CS_MQSR), U9.5 (D3)
SHIFTOUT5: U5.13 (11_MOSI_CTX1), U9.4 (D2)
SHIFTOUT6: U5.14 (12_MISO_MQSL), U9.3 (D1)
SHIFTOUT7: U5.35 (13_SCK_LED), U9.2 (D0)
UDS_n: U5.7 (5_IN2), U12.3 (A1)
VMA_n: U4.4 (A2), U5.25 (33_MCLK2)
VPA_n: U4.14 (Y4), U5.16 (24_A10_TX6_SCL2)
WR_n: U5.5 (3_LRCLK2), U12.5 (A3)

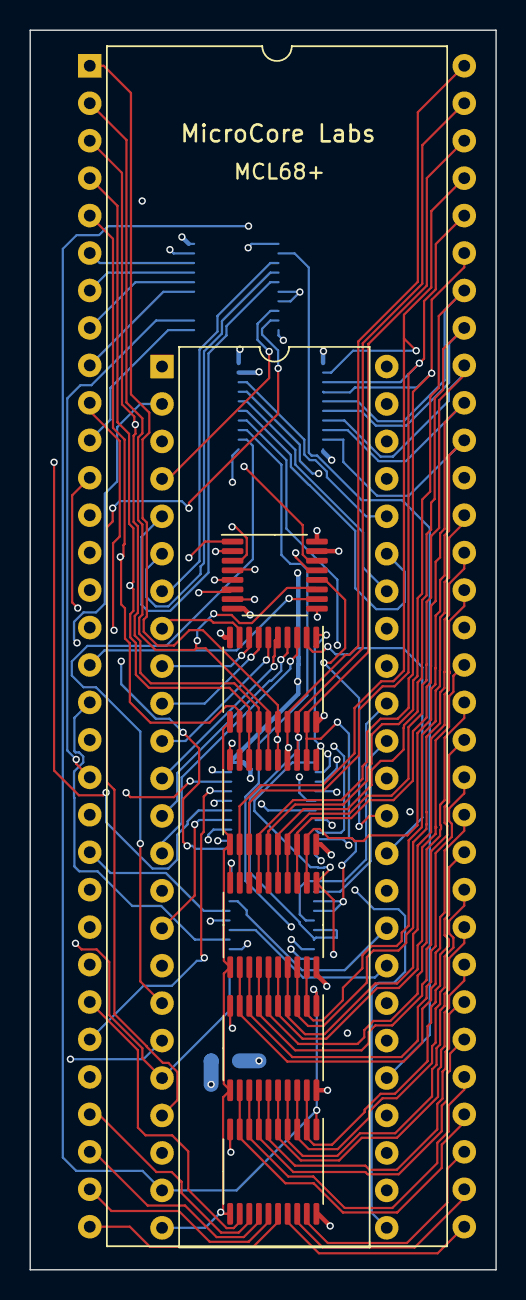
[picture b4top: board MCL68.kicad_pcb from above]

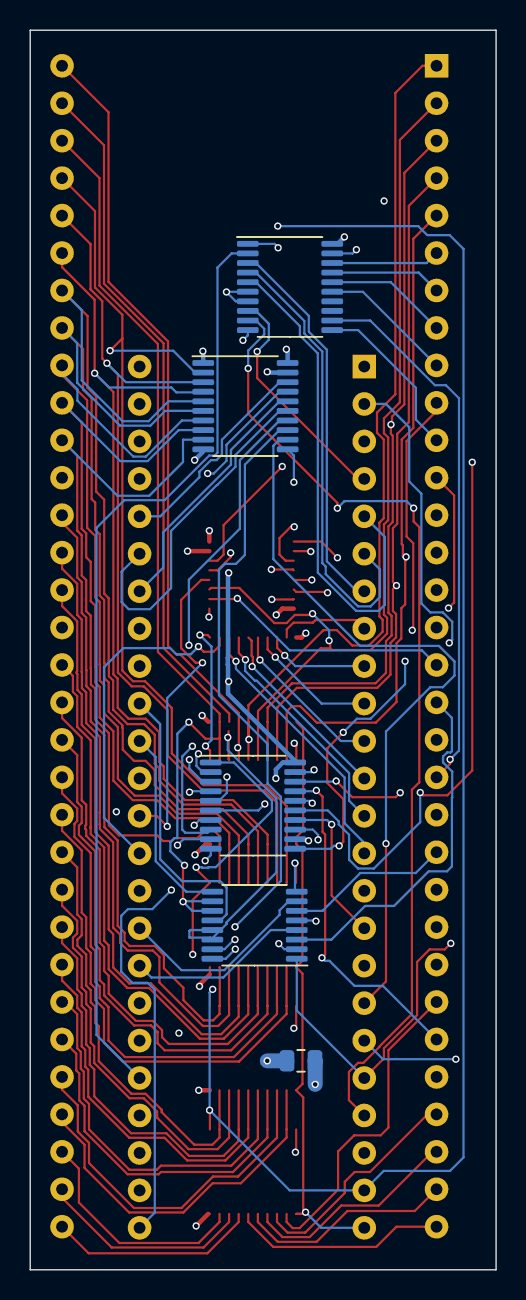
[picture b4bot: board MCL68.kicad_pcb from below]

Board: 4 copper layers, 31.6 x 84.1 mm, 13 parts (5 on the bottom side), 105 nets.

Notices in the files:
MCL8080+/MCL8080/MCL8080.ino:
Copyright (c) 2026 Ted Fried
XTMax/Code/XTMax/XTMax.ino:
Copyright (c) 2024 Ted Fried
